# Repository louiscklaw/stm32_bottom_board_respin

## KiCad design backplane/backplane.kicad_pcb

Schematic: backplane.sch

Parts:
H1, H3, H5, H7, H9: PCB1; MountingHole_5.3mm_M5_DIN965
H2, H4, H6, H8: PCB2; MountingHole_5.3mm_M5_DIN965
H10, H11, H12, H13, H14, H15: MAINBOARD; MountingHole_3.2mm_M3_DIN965
H16: HEATSINK_SCREW; MountingHole_5.3mm_M5_DIN965
H17, H18, H19, H20: STM32_MOUNT; MountingHole_3.7mm
J1: Conn_PCB1; Pin_Header_Straight_2x07_Pitch2.54mm
J2: Conn_PCB2; Pin_Header_Straight_2x07_Pitch2.54mm_horizontal_mirrored
J3: SSR_CONTROL; mpt_0,5%2f2-2,54
J4: TO_CONTROL_BOARD; JST_XH_S08B-XH-A_1x08_P2.50mm_Horizontal
J5: Conn_SSR_POWER_SOURCE; screw_terminal_01_03
J10: Conn_SSR_INPUT; screw_terminal_01_02
J12: Conn_SSR_PCB2; screw_terminal_01_03
J13: FLOW; flow_mpt_0,5%2f5-2,54
J15: AQ2; AQ_mpt_0,5%2f4-2,54
J16: AQ1; AQ_mpt_0,5%2f4-2,54
J17: O3; mpt_0,5%2f4-2,54
J18: Conn_TO_ION_AIR; Pin_Header_Straight_1x20_Pitch2.54mm
J23: PCB1_COMM_CONNECTOR; Pin_Header_Straight_1x03_Pitch2.54mm
J25: PCB1_ALARM; screw_terminal_01_03

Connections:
+5V: J4.8, J25.3; also elsewhere on the board
/220V_GND: J5.2, J12.2
/AQ1_5V: J16.2, J18.7
/AQ1_GND: J16.1, J18.8
/AQ1_SENSOR: J16.3, J18.6
/AQ1_SHIELD: J16.4, J18.5
/AQ2_5V: J15.2, J18.2
/AQ2_GND: J15.1, J18.1
/AQ2_SENSOR: J15.3, J18.3
/AQ2_SHIELD: J15.4, J18.4
/COMMON_N: J5.3, J12.3
/O3_1_24V: J17.2, J18.14
/O3_1_GND: J17.1, J18.16
/O3_1_SENSOR: J17.3, J18.12
/O3_1_SHIELD: J17.4, J18.10
/To_J1_P1: J1.1, J2.1
/To_J1_P2: J1.2, J2.2
/To_J1_P3: J1.3, J2.3
/To_J1_P4: J1.4, J2.4
/To_J1_P5: J1.5, J2.5
/To_J1_P6: J1.6, J2.6
/To_J1_P7: J1.7, J2.7
/To_J1_P8: J1.8, J2.8
/To_J1_P9: J1.9, J2.9
/To_J1_P10: J1.10, J2.10
/To_J1_P11: J1.11, J2.11
/To_J1_P12: J1.12, J2.12
/To_J1_P13: J1.13, J2.13
/To_J1_P14: J1.14, J2.14
/flow_sensor_24V: J13.2, J18.15
/flow_sensor_%RH: J13.4, J18.11
/flow_sensor_FLOW: J13.3, J18.13
/flow_sensor_GND: J13.1, J18.17
/flow_sensor_shield: J13.5, J18.9
GND: J4.1, J23.1, J25.2; also elsewhere on the board
IONAIR_RX: J4.4, J23.3; also elsewhere on the board
IONAIR_TX: J4.5, J23.2; also elsewhere on the board
PCB1_ALARM_COM: J4.6, J25.1; also elsewhere on the board
PWR_SOURCE_SSR_L_1: J5.1, J10.1; also elsewhere on the board
RELAY_N: J3.1, J4.3; also elsewhere on the board
RELAY_P: J3.2, J4.2; also elsewhere on the board
SSR_PCB2_L_2: J10.2, J12.1; also elsewhere on the board

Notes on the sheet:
the connection between pcb2 and flow sensor device
connection from PCB1 to PCB2 via backplane
MCU to ionair pcb2 control
FLOW SENSOR TERMINAL TO BOARD
1: IONAIR GND 2: IONAIR RX PIN 3: IONAIR TX PIN

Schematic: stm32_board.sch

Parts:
C1: CP1000uf,10V; CP_Elec_10x10.5
J6: 48V_SRC; JST_XH_S02B-XH-A-1_1x02_P2.50mm_Horizontal
J7: WS2812; JST_XH_S03B-XH-A-1_1x03_P2.50mm_Horizontal
J8: PURFUME; JST_XH_S02B-XH-A_1x02_P2.50mm_Horizontal
J9: SSR2; JST_XH_S02B-XH-A_1x02_P2.50mm_Horizontal
J11: FAN; JST_XH_S04B-XH-A-1_1x04_P2.50mm_Horizontal
J14: FCC_B2B; TE_84952-8_1x08-1MP_P1.0mm_Horizontal
JP1: Jumper_NO_Small; SolderJumper-2_P1.3mm_Open_TrianglePad1.0x1.5mm
R1, R2: R472,0603,NC; R_0603_1608Metric_Pad1.05x0.95mm_HandSolder

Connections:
+3V3: R1.1, R2.1; also elsewhere on the board
+5V: J14.8, JP1.1; also elsewhere on the board
/stm32_board/FAN_48V: J6.2, J11.2
/stm32_board/FAN_PWM_OUTPUT: J11.4; also elsewhere on the board
/stm32_board/FAN_RPM: J11.3; also elsewhere on the board
/stm32_board/SSR_CH1_OUTPUT1: J8.2; also elsewhere on the board
/stm32_board/SSR_CH1_OUTPUT2: J8.1; also elsewhere on the board
/stm32_board/SSR_CH2_OUTPUT1: J9.2; also elsewhere on the board
/stm32_board/SSR_CH2_OUTPUT2: J9.1; also elsewhere on the board
/stm32_board/WS2812_PWM_TERMINAL: J7.3; also elsewhere on the board
B2B_UART_RX: J14.7, R2.2; also elsewhere on the board
B2B_UART_TX: J14.6, R1.2; also elsewhere on the board
EXT_TRIGGER: J14.2; also elsewhere on the board
GND: C1.2, J6.1, J7.2, J11.1, J14.1; also elsewhere on the board
SPI1_MISO: J14.4; also elsewhere on the board
SPI1_MOSI: J14.5; also elsewhere on the board
SPI1_SCK: J14.3; also elsewhere on the board
VWS2812: C1.1, J7.1, JP1.2

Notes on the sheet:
connect the main power supply to VWS2812
the power of driver circuit is by VDD instead of +5V to provision the power control of the driver circuit
follows PC fan ordering
TO MAIN LANDING BOARD

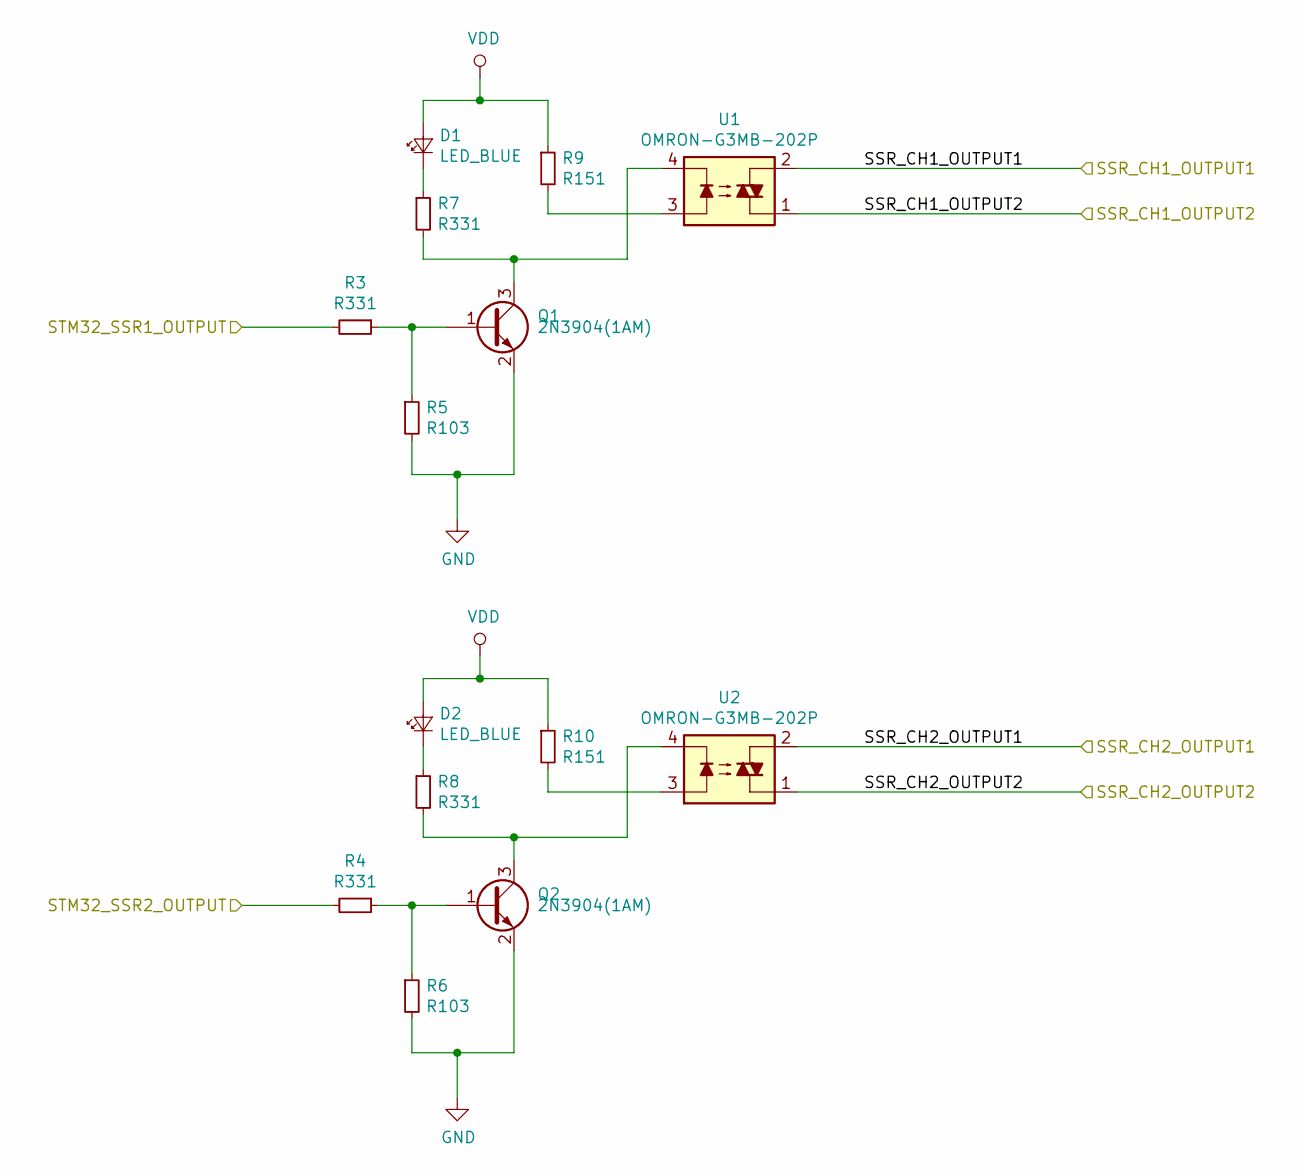
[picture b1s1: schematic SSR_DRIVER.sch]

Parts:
D1, D2: LED_BLUE; LED_0805_2012Metric_Pad1.15x1.40mm_HandSolder
Q1, Q2: 2N3904(1AM); SOT-23_Handsoldering
R3, R4, R7, R8: R331; R_0603_1608Metric_Pad1.05x0.95mm_HandSolder
R5, R6: R103; R_0603_1608Metric_Pad1.05x0.95mm_HandSolder
R9, R10: R151; R_0603_1608Metric_Pad1.05x0.95mm_HandSolder
U1, U2: OMRON-G3MB-202P

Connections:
+5V: D1.2 (A), D2.2 (A), R9.1, R10.1; also elsewhere on the board
/stm32_board/SSR_CH1_OUTPUT1: U1.2; also elsewhere on the board
/stm32_board/SSR_CH1_OUTPUT2: U1.1; also elsewhere on the board
/stm32_board/SSR_CH2_OUTPUT1: U2.2; also elsewhere on the board
/stm32_board/SSR_CH2_OUTPUT2: U2.1; also elsewhere on the board
GND: Q1.2 (E), Q2.2 (E), R5.2, R6.2; also elsewhere on the board
unnamed: D1.1 (K), R7.1
unnamed: D2.1 (K), R8.1
unnamed: Q1.1 (B), R3.1, R5.1
unnamed: Q1.3 (C), R7.2, U1.4
unnamed: Q2.1 (B), R4.1, R6.1
unnamed: Q2.3 (C), R8.2, U2.4
unnamed: R9.2, U1.3
unnamed: R10.2, U2.3
STM32_SSR1_OUTPUT: R3.2; also elsewhere on the board
STM32_SSR2_OUTPUT: R4.2; also elsewhere on the board

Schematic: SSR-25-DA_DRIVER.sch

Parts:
D3: LED_BLUE; LED_0805_2012Metric_Pad1.15x1.40mm_HandSolder
D11: SD_M7; D_SOD-123
K1: SLA-05VDC-SL-C
Q3: SS9013(J3); SOT-23_Handsoldering
R11: R103; R_0603_1608Metric_Pad1.05x0.95mm_HandSolder
R12, R13: R331; R_0603_1608Metric_Pad1.05x0.95mm_HandSolder
R14: R100; R_0603_1608Metric_Pad1.05x0.95mm_HandSolder

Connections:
+5V: D3.2 (A), R14.1; also elsewhere on the board
GND: Q3.2 (E), R12.2; also elsewhere on the board
unnamed: D3.1 (K), R13.1
unnamed: Q3.1 (B), R11.1, R12.1
PWR_SOURCE_SSR_L_1: K1.4; also elsewhere on the board
RELAY_N: D11.2, K1.2, Q3.3 (C), R13.2; also elsewhere on the board
RELAY_P: D11.1, K1.1, R14.2; also elsewhere on the board
SSR_PCB2_L_2: K1.3; also elsewhere on the board
STM32_SSR-25-DA_OUTPUT: R11.2; also elsewhere on the board

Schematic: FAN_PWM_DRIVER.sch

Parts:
D4: 1N4148; D_SOD-323_HandSoldering
Q4: SS9013_J3; SOT-23_Handsoldering
R15: R471; R_0603_1608Metric_Pad1.05x0.95mm_HandSolder
R16: R103; R_0603_1608Metric_Pad1.05x0.95mm_HandSolder
R17: R331; R_0603_1608Metric_Pad1.05x0.95mm_HandSolder

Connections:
+5V: R16.1, R17.1; also elsewhere on the board
/stm32_board/FAN_PWM_OUTPUT: Q4.3 (C), R17.2; also elsewhere on the board
/stm32_board/FAN_RPM: D4.1; also elsewhere on the board
GND: Q4.2 (E); also elsewhere on the board
unnamed: Q4.1 (B), R15.1
STM32_FAN_PWM_OUTPUT: R15.2; also elsewhere on the board
STM32_FAN_RPM: D4.2, R16.2; also elsewhere on the board

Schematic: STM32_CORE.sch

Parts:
BOOT0, BOOT1: JUMPER; SolderJumper-3_P2.0mm_Open_TrianglePad1.0x1.5mm
C2, C3, C4, C5, C6: C104; C_0603_1608Metric_Pad1.05x0.95mm_HandSolder
C7: CP220uf,50V; CP_Elec_10x10.5
C8, C9: TC106,10V; CP_EIA-3216-12_Kemet-S_Pad1.58x1.35mm_HandSolder
C10, C11: C105; C_0603_1608Metric_Pad1.05x0.95mm_HandSolder
C12, C13, C14, C15: C20pf; C_0603_1608Metric_Pad1.05x0.95mm_HandSolder
D5: LED_GREEN; LED_0603_1608Metric_Pad1.05x0.95mm_HandSolder
D6: LED_GREEN; LED_0805_2012Metric_Pad1.15x1.40mm_HandSolder
D7: LED_ORANGE; LED_0805_2012Metric_Pad1.15x1.40mm_HandSolder
J22: POWER; JST_XH_S03B-XH-A-1_1x03_P2.50mm_Horizontal
J24: Conn_01x14; Pin_Header_Straight_1x14_Pitch1.27mm
J26: Conn_01x12; Pin_Header_Straight_1x12_Pitch1.27mm
J27: Conn_01x15; Pin_Header_Straight_1x15_Pitch1.27mm
R18: R102,0603; R_0603_1608Metric_Pad1.05x0.95mm_HandSolder
R19, R20: R104; R_0603_1608Metric_Pad1.05x0.95mm_HandSolder
R21, R23: R511; R_0603_1608Metric_Pad1.05x0.95mm_HandSolder
R22: R103; R_0603_1608Metric_Pad1.05x0.95mm_HandSolder
SW1: SW_Push; SW_SPST_PTS645
U3: waveshare-swd-pinsocket
U4: STM32F103C8T6; LQFP-48_7x7mm_P0.5mm
U5: AMS1117-3.3; SOT-223-3_TabPin2
Y1: O8M; hc-49_smd
Y2: O_EPSON_32.768K; MC-306

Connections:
+3V3: BOOT0.1 (A), BOOT1.1 (A), C2.1, C3.1, C4.1, C5.1, C6.1, C9.1, C10.1, D7.2 (A), J22.3, R22.1, U3.7, U3.8, U4.1 (VBAT), U4.9 (VCC3V3), U4.24 (VDD_1), U4.36 (VDD_2), U4.48 (VCC3V3), U5.2 (VO); also elsewhere on the board
+5V: C7.1, C8.1, D6.2 (A), J22.2, J24.1, U5.3 (VI); also elsewhere on the board
/stm32_board/STM32_CORE/BOOT0: R19.2, U4.44 (BOOT0)
/stm32_board/STM32_CORE/BOOT1: R20.1, U4.20 (PB2/BOOT1)
/stm32_board/STM32_CORE/OSCIN: C13.1, U4.5 (OSCIN), Y1.2
/stm32_board/STM32_CORE/OSCOUT: C12.1, U4.6 (OSCOUT), Y1.1
/stm32_board/STM32_CORE/PA0: U4.10 (PA0)
/stm32_board/STM32_CORE/PA1: U4.11 (PA1)
/stm32_board/STM32_CORE/PA4: U4.14 (PA4)
/stm32_board/STM32_CORE/PA10: J26.7, U4.31 (PA10)
/stm32_board/STM32_CORE/PA15: J24.5, U4.38 (PA15)
/stm32_board/STM32_CORE/PB8: J24.11, U4.45 (PB8)
/stm32_board/STM32_CORE/PB9: J24.12, U4.46 (PB9)
/stm32_board/STM32_CORE/PB13: J26.2, U4.26 (PB13)
/stm32_board/STM32_CORE/PB14: J26.3, U4.27 (PB14)
/stm32_board/STM32_CORE/PB15: J26.4, U4.28 (PB15)
/stm32_board/STM32_CORE/PC13: J24.13, R18.1, U4.2 (PC13)
/stm32_board/STM32_CORE/PC14: C15.1, U4.3 (PC14), Y2.1
/stm32_board/STM32_CORE/PC15: C14.1, U4.4 (PC15), Y2.4
/stm32_board/STM32_CORE/RESET: C11.1, R22.2, SW1.2, U4.7 (RESET)
/stm32_board/STM32_CORE/RST: U3.1
/stm32_board/STM32_CORE/SWCLK: J24.3, U3.6, U4.37 (SWCLK)
/stm32_board/STM32_CORE/SWIM: U3.5
/stm32_board/STM32_CORE/SWIO: J24.2, U3.2, U4.34 (SWIO)
B2B_UART_RX: J24.10, U4.43 (PB7); also elsewhere on the board
B2B_UART_TX: J24.9, U4.42 (PB6); also elsewhere on the board
EXT_TRIGGER: J26.6, U4.30 (PA9); also elsewhere on the board
GND: BOOT0.3 (B), BOOT1.3 (B), C2.2, C3.2, C4.2, C5.2, C6.2, C7.2, C8.2, C9.2, C10.2, C11.2, C12.2, C13.2, C14.2, C15.2, D5.1 (K), J22.1, J24.4, R21.2, R23.2, SW1.1, U3.3, U3.4, U4.8 (GND), U4.23 (VSS_1), U4.35 (VSS_2), U4.47 (GND), U5.1 (GND); also elsewhere on the board
IONAIR-TTL-RX: U4.13 (PA3); also elsewhere on the board
IONAIR-TTL-TX: U4.12 (PA2); also elsewhere on the board
unnamed: BOOT0.2 (C), R19.1
unnamed: BOOT1.2 (C), R20.2
unnamed: D5.2 (A), R18.2
unnamed: D6.1 (K), R21.1
unnamed: D7.1 (K), R23.1
SPI1_MISO: J24.7, U4.40 (PB4); also elsewhere on the board
SPI1_MOSI: J24.8, U4.41 (PB5); also elsewhere on the board
SPI1_SCK: J24.6, U4.39 (PB3); also elsewhere on the board
STM32_FAN_PWM_OUTPUT: J26.5, U4.29 (PA8); also elsewhere on the board
STM32_FAN_RPM: J26.1, U4.25 (PB12); also elsewhere on the board
STM32_PCB1_ALARM_COM: U4.15 (PA5); also elsewhere on the board
STM32_PMS7003S_RESET: J26.8, U4.32 (PA11); also elsewhere on the board
STM32_PMS7003S_RXD: U4.22 (PB11); also elsewhere on the board
STM32_PMS7003S_SET: J26.9, U4.33 (PA12); also elsewhere on the board
STM32_PMS7003S_TXD: U4.21 (PB10); also elsewhere on the board
STM32_SSR1_OUTPUT: U4.18 (PB0); also elsewhere on the board
STM32_SSR2_OUTPUT: U4.17 (PA7); also elsewhere on the board
STM32_SSR-25-DA_OUTPUT: U4.19 (PB1); also elsewhere on the board
STM32_WS2812_OUTPUT: U4.16 (PA6); also elsewhere on the board

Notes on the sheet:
to stablize power from power supply ->
update to incidate the +3V3 is not necessary

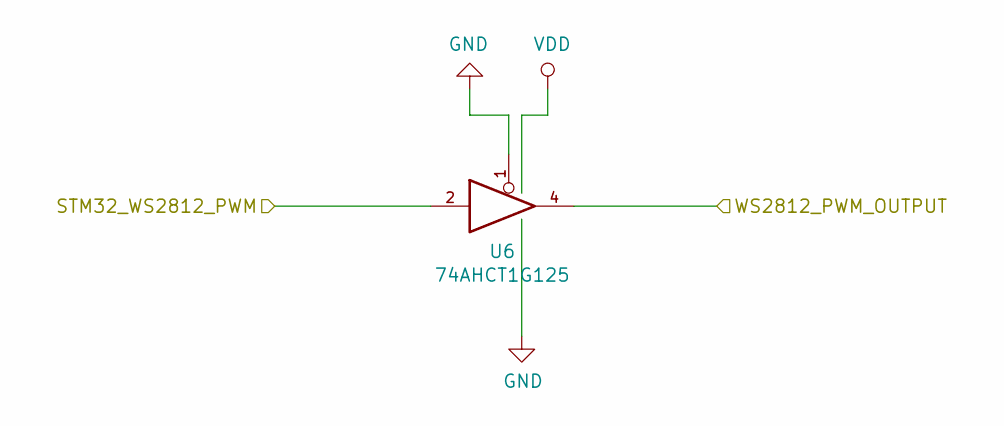
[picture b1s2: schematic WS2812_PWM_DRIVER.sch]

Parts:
U6: 74AHCT1G125; SOT-23-5_HandSoldering

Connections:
+5V: U6.5 (VCC); also elsewhere on the board
/stm32_board/WS2812_PWM_TERMINAL: U6.4; also elsewhere on the board
GND: U6.1, U6.3 (GND); also elsewhere on the board
STM32_WS2812_OUTPUT: U6.2; also elsewhere on the board

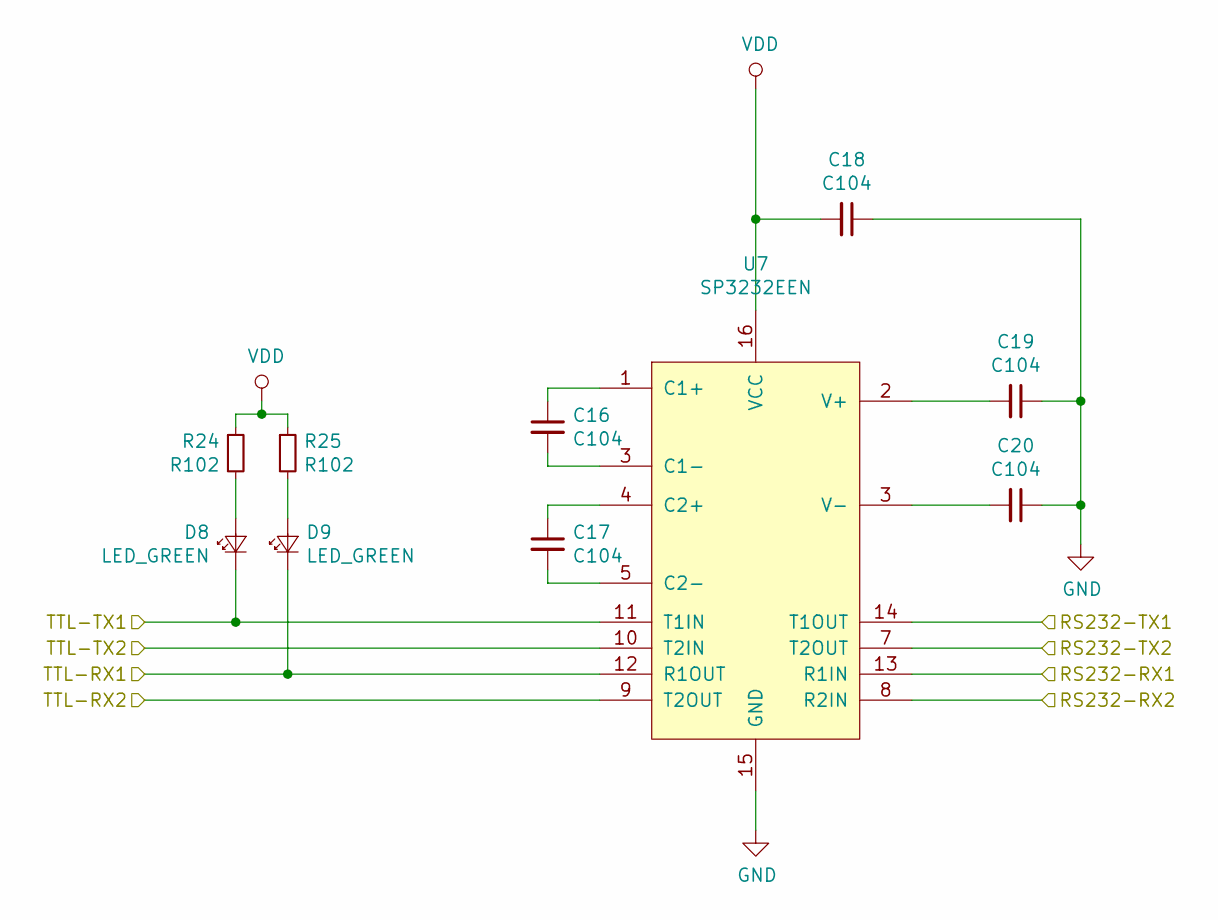
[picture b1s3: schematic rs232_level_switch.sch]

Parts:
C16, C17, C18, C19, C20: C104; C_0805_2012Metric_Pad1.15x1.40mm_HandSolder
D8, D9: LED_GREEN; LED_0805_2012Metric_Pad1.15x1.40mm_HandSolder
R24, R25: R102; R_0603_1608Metric_Pad1.05x0.95mm_HandSolder
U7: SP3232EEN; SOP-16_4.4x10.4mm_Pitch1.27mm

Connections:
+5V: C18.2, R24.1, R25.1, U7.16 (VCC); also elsewhere on the board
/stm32_board/rs232_level_switch/RS232-RX2: U7.8 (R2IN)
/stm32_board/rs232_level_switch/RS232-TX2: U7.7 (T2OUT)
/stm32_board/rs232_level_switch/TTL-RX2: U7.9 (T2OUT)
/stm32_board/rs232_level_switch/TTL-TX2: U7.10 (T2IN)
GND: C18.1, C19.1, C20.1, U7.15 (GND); also elsewhere on the board
IONAIR-TTL-RX: D9.1 (K), U7.12 (R1OUT); also elsewhere on the board
IONAIR-TTL-TX: D8.1 (K), U7.11 (T1IN); also elsewhere on the board
IONAIR_RX: U7.13 (R1IN); also elsewhere on the board
IONAIR_TX: U7.14 (T1OUT); also elsewhere on the board
unnamed: C16.1, U7.1 (C1+)
unnamed: C17.1, U7.4 (C2+)
unnamed: C17.2, U7.5 (C2-)
unnamed: C19.2, U7.2 (V+)
unnamed: D8.2 (A), R24.2
unnamed: D9.2 (A), R25.2

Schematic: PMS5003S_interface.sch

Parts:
C21: CP100uf,10V; CP_Elec_6.3x5.2
J28: PMS7003S_CONN; JST_XH_S08B-XH-A_1x08_P2.50mm_Horizontal
R26, R27: R103,0603; R_0603_1608Metric_Pad1.05x0.95mm_HandSolder

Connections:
+3V3: R26.2, R27.1; also elsewhere on the board
+5V: C21.1, J28.1; also elsewhere on the board
GND: C21.2, J28.2, J28.8; also elsewhere on the board
STM32_PMS7003S_RESET: J28.3, R27.2; also elsewhere on the board
STM32_PMS7003S_RXD: J28.5; also elsewhere on the board
STM32_PMS7003S_SET: J28.6, R26.1; also elsewhere on the board
STM32_PMS7003S_TXD: J28.4; also elsewhere on the board

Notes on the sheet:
PMS7003S interfacing

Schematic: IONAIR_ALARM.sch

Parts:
D10: 1N4148; D_SOD-323_HandSoldering
R28: R103; R_0603_1608Metric_Pad1.05x0.95mm_HandSolder

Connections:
+5V: R28.1; also elsewhere on the board
PCB1_ALARM_COM: D10.1; also elsewhere on the board
STM32_PCB1_ALARM_COM: D10.2, R28.2; also elsewhere on the board

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
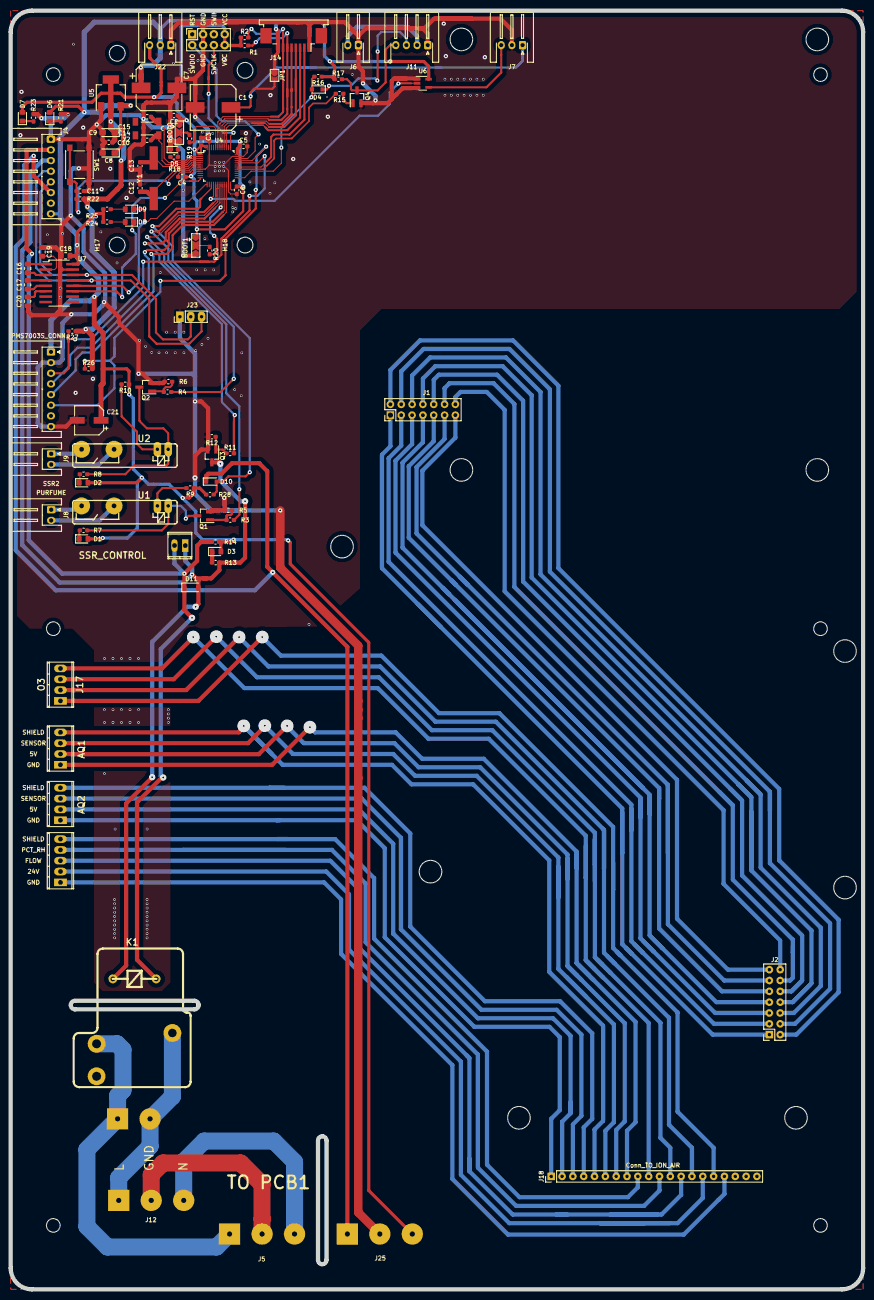
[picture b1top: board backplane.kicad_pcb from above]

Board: 2 copper layers, 200.0 x 300.0 mm, 120 parts (0 on the bottom side), 105 nets.

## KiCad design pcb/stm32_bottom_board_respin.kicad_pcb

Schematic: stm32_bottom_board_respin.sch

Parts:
C1: CP1000uf,10V; CP_Elec_10x10.5
J1: 48V_SRC; s2b-ph-kl
J2: WS2812_CTRL; s3b-ph-kl
J3: FAN_CTRL; s4b-ph-kl
J4: SSR_OUTPUT; s2b-ph-kl
J5: PURFUME_CTRL; s2b-ph-kl
J9: PCB_UART; s3b-ph-kl
J10: FCC_B2B; TE_84952-8_1x08-1MP_P1.0mm_Horizontal
J11: SSR2_CTRL; s2b-ph-kl
J14: MAINBOARD_CONN; s8b-ph-kl
R5, R6: R472,0603,NC; R_0603_1608Metric_Pad1.05x0.95mm_HandSolder

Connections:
+3V3: R5.1, R6.1; also elsewhere on the board
+5V: J10.1, J14.8; also elsewhere on the board
/FAN_48V: J1.2, J3.2
/FAN_PWM_OUTPUT: J3.4; also elsewhere on the board
/FAN_RPM: J3.3; also elsewhere on the board
/IONAIR_RX: J9.1, J14.4; also elsewhere on the board
/IONAIR_TX: J9.2, J14.5; also elsewhere on the board
/SSR-25-DA_N: J4.1, J14.3; also elsewhere on the board
/SSR-25-DA_P: J4.2, J14.2; also elsewhere on the board
/SSR_CH1_OUTPUT1: J5.2; also elsewhere on the board
/SSR_CH1_OUTPUT2: J5.1; also elsewhere on the board
/SSR_CH2_OUTPUT1: J11.2; also elsewhere on the board
/SSR_CH2_OUTPUT2: J11.1; also elsewhere on the board
/WS2812_PWM_TERMINAL: J2.3; also elsewhere on the board
B2B_UART_RX: J10.7, R6.2; also elsewhere on the board
B2B_UART_TX: J10.6, R5.2; also elsewhere on the board
GND: C1.2, J1.1, J2.2, J3.1, J9.3, J10.2, J10.8, J14.1; also elsewhere on the board
PCB1_ALARM_COM: J14.6; also elsewhere on the board
SPI1_MISO: J10.4; also elsewhere on the board
SPI1_MOSI: J10.5; also elsewhere on the board
SPI1_SCK: J10.3; also elsewhere on the board
VWS2812: C1.1, J2.1

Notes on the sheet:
connect the main power supply to VWS2812
the power of driver circuit is by VDD instead of +5V to provision the power control of the driver circuit
follows PC fan ordering
TO MAIN LANDING BOARD

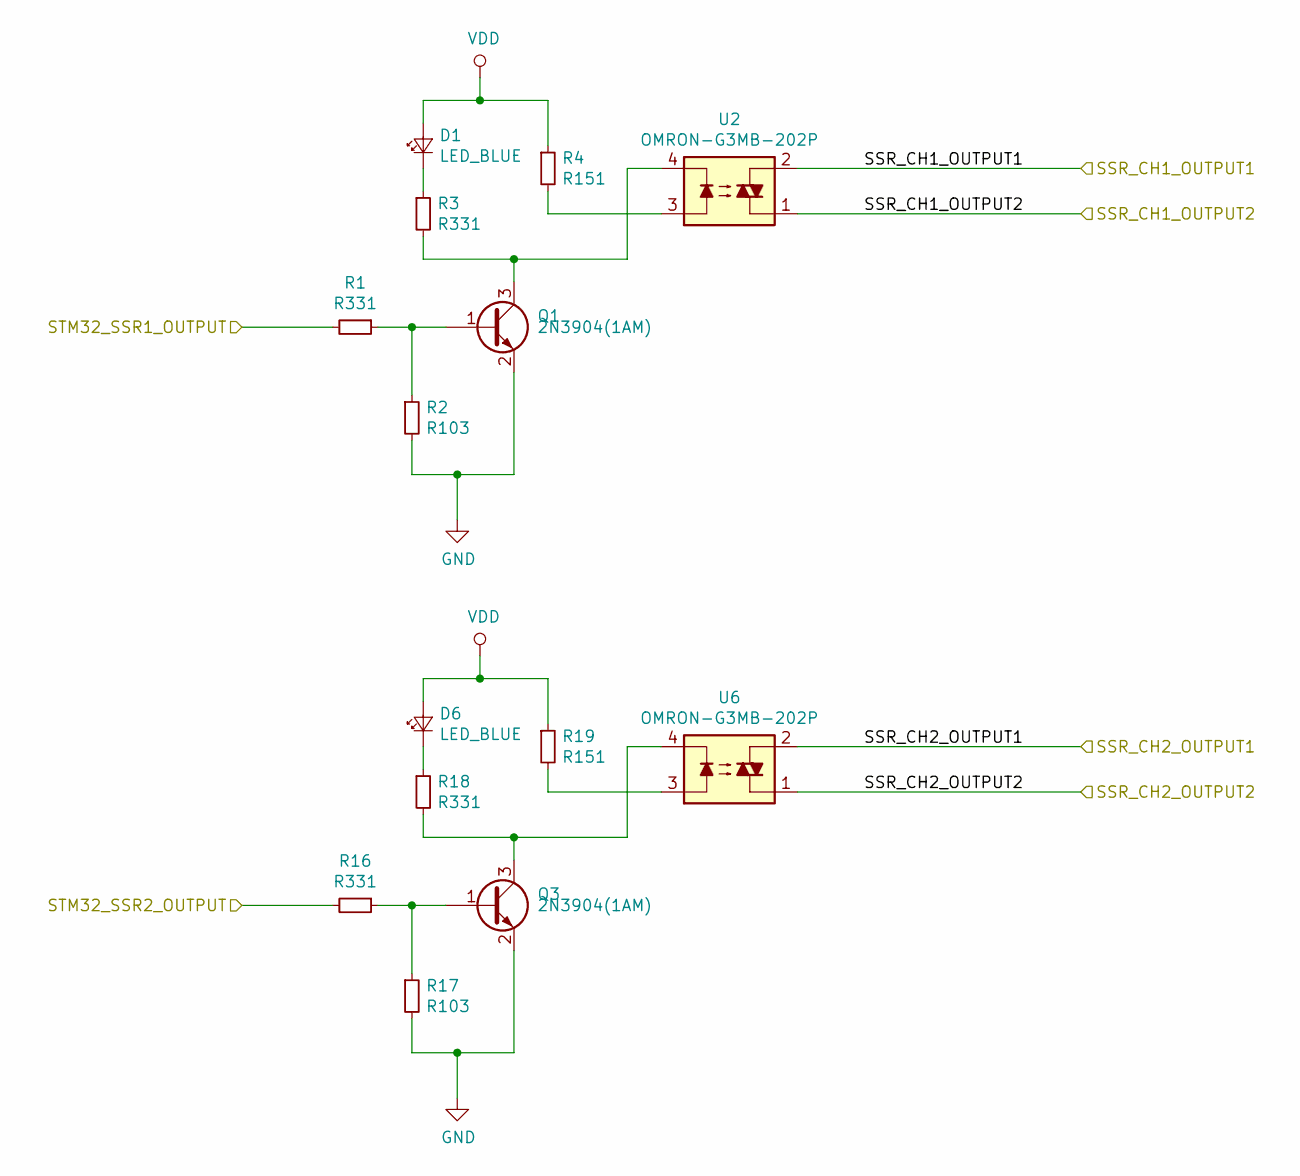
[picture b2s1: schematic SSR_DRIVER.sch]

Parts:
D1, D6: LED_BLUE; LED_0805_2012Metric_Pad1.15x1.40mm_HandSolder
Q1, Q3: 2N3904(1AM); SOT-23_Handsoldering
R1, R3, R16, R18: R331; R_0603_1608Metric_Pad1.05x0.95mm_HandSolder
R2, R17: R103; R_0603_1608Metric_Pad1.05x0.95mm_HandSolder
R4, R19: R151; R_0603_1608Metric_Pad1.05x0.95mm_HandSolder
U2, U6: OMRON-G3MB-202P

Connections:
+5V: D1.2 (A), D6.2 (A), R4.1, R19.1; also elsewhere on the board
/SSR_CH1_OUTPUT1: U2.2; also elsewhere on the board
/SSR_CH1_OUTPUT2: U2.1; also elsewhere on the board
/SSR_CH2_OUTPUT1: U6.2; also elsewhere on the board
/SSR_CH2_OUTPUT2: U6.1; also elsewhere on the board
GND: Q1.2 (E), Q3.2 (E), R2.2, R17.2; also elsewhere on the board
unnamed: D1.1 (K), R3.1
unnamed: D6.1 (K), R18.1
unnamed: Q1.1 (B), R1.1, R2.1
unnamed: Q1.3 (C), R3.2, U2.4
unnamed: Q3.1 (B), R16.1, R17.1
unnamed: Q3.3 (C), R18.2, U6.4
unnamed: R4.2, U2.3
unnamed: R19.2, U6.3
STM32_SSR1_OUTPUT: R1.2; also elsewhere on the board
STM32_SSR2_OUTPUT: R16.2; also elsewhere on the board

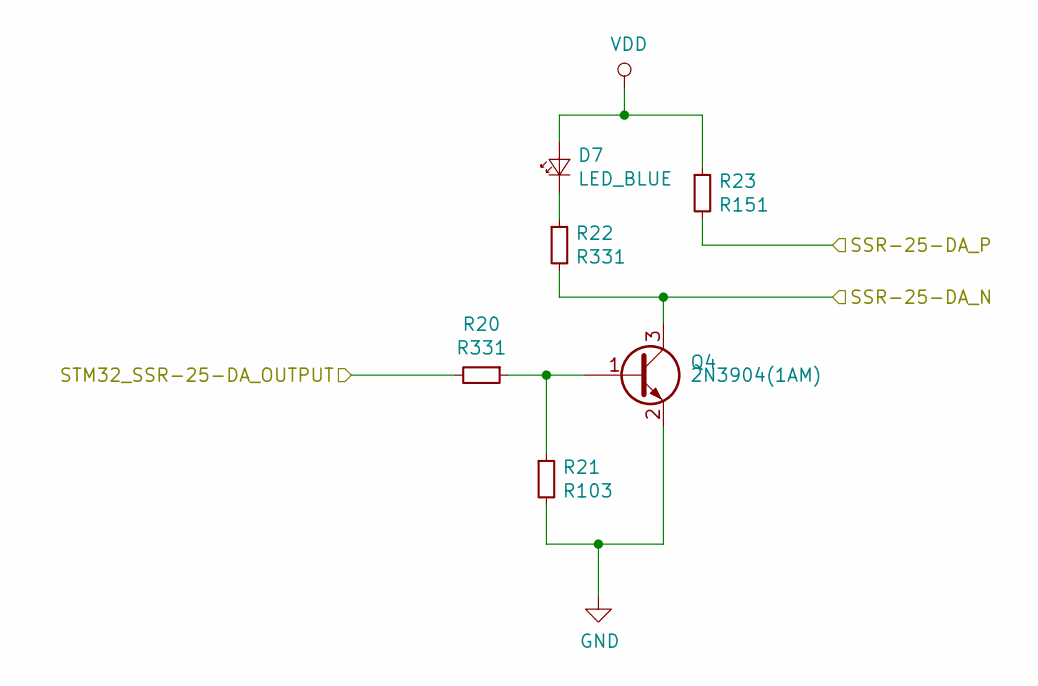
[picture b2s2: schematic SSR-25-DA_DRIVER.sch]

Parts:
D7: LED_BLUE; LED_0805_2012Metric_Pad1.15x1.40mm_HandSolder
Q4: 2N3904(1AM); SOT-23_Handsoldering
R20, R22: R331; R_0603_1608Metric_Pad1.05x0.95mm_HandSolder
R21: R103; R_0603_1608Metric_Pad1.05x0.95mm_HandSolder
R23: R151; R_0603_1608Metric_Pad1.05x0.95mm_HandSolder

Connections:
+5V: D7.2 (A), R23.1; also elsewhere on the board
/SSR-25-DA_N: Q4.3 (C), R22.2; also elsewhere on the board
/SSR-25-DA_P: R23.2; also elsewhere on the board
GND: Q4.2 (E), R21.2; also elsewhere on the board
unnamed: D7.1 (K), R22.1
unnamed: Q4.1 (B), R20.1, R21.1
STM32_SSR-25-DA_OUTPUT: R20.2; also elsewhere on the board

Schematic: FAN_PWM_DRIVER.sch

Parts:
D8: 1N4148; D_SOD-323_HandSoldering
Q2: SS9013_J3; SOT-23_Handsoldering
R7: R471; R_0603_1608Metric_Pad1.05x0.95mm_HandSolder
R8: R331; R_0603_1608Metric_Pad1.05x0.95mm_HandSolder
R24: R103; R_0603_1608Metric_Pad1.05x0.95mm_HandSolder

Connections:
+5V: R8.1, R24.1; also elsewhere on the board
/FAN_PWM_OUTPUT: Q2.3 (C), R8.2; also elsewhere on the board
/FAN_RPM: D8.1; also elsewhere on the board
GND: Q2.2 (E); also elsewhere on the board
unnamed: Q2.1 (B), R7.1
STM32_FAN_PWM_OUTPUT: R7.2; also elsewhere on the board
STM32_FAN_RPM: D8.2, R24.2; also elsewhere on the board

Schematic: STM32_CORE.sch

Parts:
BOOT0, BOOT1: JUMPER; SolderJumper-3_P2.0mm_Open_TrianglePad1.0x1.5mm
C2, C3, C4, C5, C6: C104; C_0603_1608Metric_Pad1.05x0.95mm_HandSolder
C7, C8: TC106,10V; CP_EIA-3216-12_Kemet-S_Pad1.58x1.35mm_HandSolder
C9, C10: C105; C_0603_1608Metric_Pad1.05x0.95mm_HandSolder
C11, C12, C13, C14: C20pf; C_0603_1608Metric_Pad1.05x0.95mm_HandSolder
C20: CP220uf,50V; CP_Elec_10x10.5
D2: LED_GREEN; LED_0805_2012Metric_Pad1.15x1.40mm_HandSolder
D3: LED_ORANGE; LED_0805_2012Metric_Pad1.15x1.40mm_HandSolder
D9: LED_GREEN; LED_0603_1608Metric_Pad1.05x0.95mm_HandSolder
J6: Conn_01x14; Pin_Header_Straight_1x14_Pitch1.27mm
J7: Conn_01x12; Pin_Header_Straight_1x12_Pitch1.27mm
J8: Conn_01x15; Pin_Header_Straight_1x15_Pitch1.27mm
J12: POWER; s3b-ph-kl
R9, R10: R104; R_0603_1608Metric_Pad1.05x0.95mm_HandSolder
R11, R13: R511; R_0603_1608Metric_Pad1.05x0.95mm_HandSolder
R12: R103; R_0603_1608Metric_Pad1.05x0.95mm_HandSolder
R27: R102,0603; R_0603_1608Metric_Pad1.05x0.95mm_HandSolder
SW1: SW_Push; SW_SPST_PTS645
U3: STM32F103C8T6; LQFP-48_7x7mm_P0.5mm
U4: AMS1117-3.3; SOT-223-3_TabPin2
U7: waveshare-swd-pinsocket
Y1: O8M; hc-49_smd
Y2: O_EPSON_32.768K; MC-306

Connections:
+3V3: BOOT0.1 (A), BOOT1.1 (A), C2.1, C3.1, C4.1, C5.1, C6.1, C8.1, C9.1, D3.2 (A), J8.2, J12.3, R12.1, U3.1 (VBAT), U3.9 (VCC3V3), U3.24 (VDD_1), U3.36 (VDD_2), U3.48 (VCC3V3), U4.2 (VO), U7.7, U7.8; also elsewhere on the board
+5V: C7.1, C20.1, D2.2 (A), J6.1, J12.2, U4.3 (VI); also elsewhere on the board
/STM32_CORE/BOOT0: R9.2, U3.44 (BOOT0)
/STM32_CORE/BOOT1: R10.1, U3.20 (PB2/BOOT1)
/STM32_CORE/OSCIN: C12.1, U3.5 (OSCIN), Y1.2
/STM32_CORE/OSCOUT: C11.1, U3.6 (OSCOUT), Y1.1
/STM32_CORE/PA0: J8.4, U3.10 (PA0)
/STM32_CORE/PA1: J8.5, U3.11 (PA1)
/STM32_CORE/PA4: J8.8, U3.14 (PA4)
/STM32_CORE/PA9: J7.6, U3.30 (PA9)
/STM32_CORE/PA10: J7.7, U3.31 (PA10)
/STM32_CORE/PA15: J6.5, U3.38 (PA15)
/STM32_CORE/PB8: J6.11, U3.45 (PB8)
/STM32_CORE/PB9: J6.12, U3.46 (PB9)
/STM32_CORE/PB13: J7.2, U3.26 (PB13)
/STM32_CORE/PB14: J7.3, U3.27 (PB14)
/STM32_CORE/PB15: J7.4, U3.28 (PB15)
/STM32_CORE/PC13: J6.13, R27.1, U3.2 (PC13)
/STM32_CORE/PC14: C14.1, U3.3 (PC14), Y2.1
/STM32_CORE/PC15: C13.1, U3.4 (PC15), Y2.4
/STM32_CORE/RESET: C10.1, R12.2, SW1.2, U3.7 (RESET)
/STM32_CORE/RST: U7.1
/STM32_CORE/SWCLK: J6.3, U3.37 (SWCLK), U7.6
/STM32_CORE/SWIM: U7.5
/STM32_CORE/SWIO: J6.2, U3.34 (SWIO), U7.2
B2B_UART_RX: J6.10, U3.43 (PB7); also elsewhere on the board
B2B_UART_TX: J6.9, U3.42 (PB6); also elsewhere on the board
GND: BOOT0.3 (B), BOOT1.3 (B), C2.2, C3.2, C4.2, C5.2, C6.2, C7.2, C8.2, C9.2, C10.2, C11.2, C12.2, C13.2, C14.2, C20.2, D9.1 (K), J6.4, J8.1, J12.1, R11.2, R13.2, SW1.1, U3.8 (GND), U3.23 (VSS_1), U3.35 (VSS_2), U3.47 (GND), U4.1 (GND), U7.3, U7.4; also elsewhere on the board
IONAIR-TTL-RX: J8.7, U3.13 (PA3); also elsewhere on the board
IONAIR-TTL-TX: J8.6, U3.12 (PA2); also elsewhere on the board
unnamed: BOOT0.2 (C), R9.1
unnamed: BOOT1.2 (C), R10.2
unnamed: D2.1 (K), R11.1
unnamed: D3.1 (K), R13.1
unnamed: D9.2 (A), R27.2
PCB1_ALARM_COM: J8.9, U3.15 (PA5); also elsewhere on the board
SPI1_MISO: J6.7, U3.40 (PB4); also elsewhere on the board
SPI1_MOSI: J6.8, U3.41 (PB5); also elsewhere on the board
SPI1_SCK: J6.6, U3.39 (PB3); also elsewhere on the board
STM32_FAN_PWM_OUTPUT: J7.5, U3.29 (PA8); also elsewhere on the board
STM32_FAN_RPM: J7.1, U3.25 (PB12); also elsewhere on the board
STM32_PMS7003S_RESET: J7.8, U3.32 (PA11); also elsewhere on the board
STM32_PMS7003S_RXD: J8.15, U3.22 (PB11); also elsewhere on the board
STM32_PMS7003S_SET: J7.9, U3.33 (PA12); also elsewhere on the board
STM32_PMS7003S_TXD: J8.14, U3.21 (PB10); also elsewhere on the board
STM32_SSR1_OUTPUT: J8.12, U3.18 (PB0); also elsewhere on the board
STM32_SSR2_OUTPUT: J8.11, U3.17 (PA7); also elsewhere on the board
STM32_SSR-25-DA_OUTPUT: J8.13, U3.19 (PB1); also elsewhere on the board
STM32_WS2812_OUTPUT: J8.10, U3.16 (PA6); also elsewhere on the board

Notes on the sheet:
to stablize power from power supply ->
update to incidate the +3V3 is not necessary

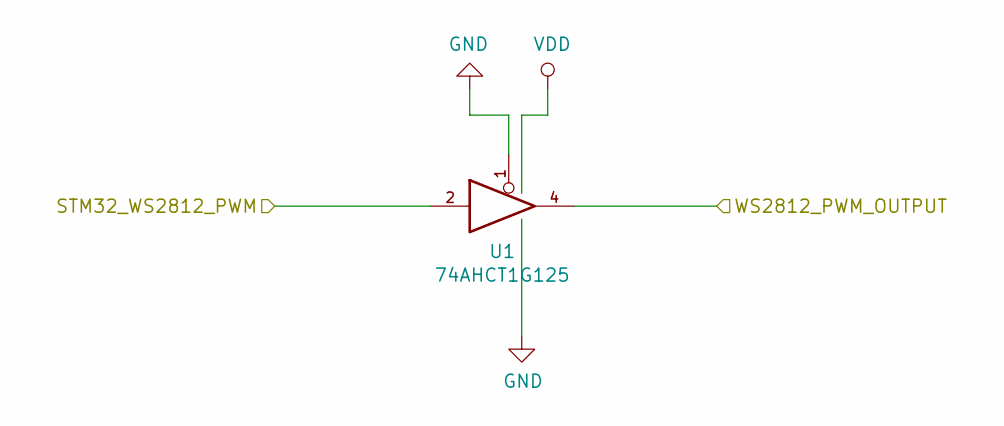
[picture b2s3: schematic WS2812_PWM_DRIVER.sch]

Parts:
U1: 74AHCT1G125; SOT-23-5_HandSoldering

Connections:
+5V: U1.5 (VCC); also elsewhere on the board
/WS2812_PWM_TERMINAL: U1.4; also elsewhere on the board
GND: U1.1, U1.3 (GND); also elsewhere on the board
STM32_WS2812_OUTPUT: U1.2; also elsewhere on the board

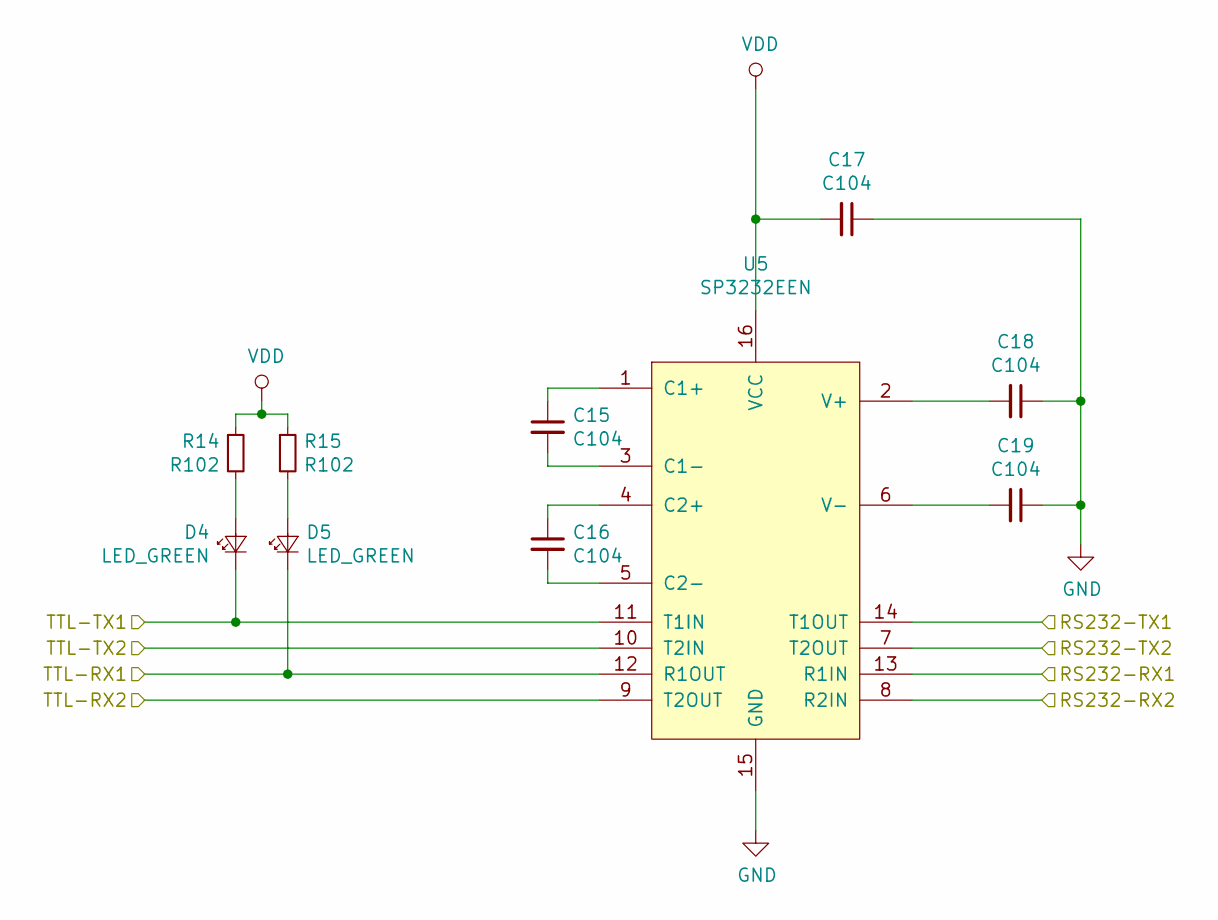
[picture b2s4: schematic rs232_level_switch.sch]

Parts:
C15, C16, C17, C18, C19: C104; C_0805_2012Metric_Pad1.15x1.40mm_HandSolder
D4, D5: LED_GREEN; LED_0805_2012Metric_Pad1.15x1.40mm_HandSolder
R14, R15: R102; R_0603_1608Metric_Pad1.05x0.95mm_HandSolder
U5: SP3232EEN; SOP-16_4.4x10.4mm_Pitch1.27mm

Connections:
+5V: C17.2, R14.1, R15.1, U5.16 (VCC); also elsewhere on the board
/IONAIR_RX: U5.13 (R1IN); also elsewhere on the board
/IONAIR_TX: U5.14 (T1OUT); also elsewhere on the board
/rs232_level_switch/RS232-RX2: U5.8 (R2IN)
/rs232_level_switch/RS232-TX2: U5.7 (T2OUT)
/rs232_level_switch/TTL-RX2: U5.9 (T2OUT)
/rs232_level_switch/TTL-TX2: U5.10 (T2IN)
GND: C17.1, C18.1, C19.1, U5.15 (GND); also elsewhere on the board
IONAIR-TTL-RX: D5.1 (K), U5.12 (R1OUT); also elsewhere on the board
IONAIR-TTL-TX: D4.1 (K), U5.11 (T1IN); also elsewhere on the board
unnamed: C15.1, U5.1 (C1+)
unnamed: C15.2, U5.3 (C1-)
unnamed: C16.1, U5.4 (C2+)
unnamed: C16.2, U5.5 (C2-)
unnamed: C18.2, U5.2 (V+)
unnamed: C19.2, U5.6 (V-)
unnamed: D4.2 (A), R14.2
unnamed: D5.2 (A), R15.2

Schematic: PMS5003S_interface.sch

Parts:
C21: CP100uf,10V; CP_Elec_6.3x5.2
J13: PMS7003S_CONN; s8b-ph-kl
R25, R26: R103,0603; R_0603_1608Metric_Pad1.05x0.95mm_HandSolder

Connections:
+3V3: R25.2, R26.1; also elsewhere on the board
+5V: C21.1, J13.1; also elsewhere on the board
GND: C21.2, J13.2, J13.8; also elsewhere on the board
STM32_PMS7003S_RESET: J13.3, R26.2; also elsewhere on the board
STM32_PMS7003S_RXD: J13.5; also elsewhere on the board
STM32_PMS7003S_SET: J13.6, R25.1; also elsewhere on the board
STM32_PMS7003S_TXD: J13.4; also elsewhere on the board

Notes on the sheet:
PMS7003S interfacing
